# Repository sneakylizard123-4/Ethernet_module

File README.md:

# W5500 Ethernet Module

A small SPI Ethernet breakout for the W5500.

## Features

- SPI interface
- 10/100 Ethernet
- 4-layer board with ground and 3.3V planes
- Split analog/digital supply with ferrite bead
- On-board and jack LEDs
- 25 MHz crystal

## PCB

50.0 x 21.4 mm, 4-layer, 1.6 mm FR-4.

## Schematic

## Pinout

| Pin | Name | Notes |
|---|---|---|
| 1 | GND | Ground |
| 2 | 3.3V | Power in |
| 3 | SCS | Chip select (active low) |
| 4 | SCLK | SPI clock |
| 5 | MISO | SPI MISO |
| 6 | MOSI | SPI MOSI |
| 7 | INT | Interrupt (active low) |
| 8 | RST | Reset (active low) |

## BOM

| Ref | Value | MPN | Manufacturer | Qty | Unit $ | Ext $ | Supplier Link |
|-----|-------|-----|--------------|-----|--------|-------|---------------|
| C1,C4,C6,C8,C10,C11,C13 | 0.1uF 50V X7R 0603 | CL10B104KB8NNNC | Samsung Electro-Mechanics | 7 | 0.0088 | 0.0616 | [LCSC](https://www.lcsc.com/product-detail/Samsung-Electro-Mechanics-CL10B104KB8NNNC_C1591.html) |
| C9,C12 | 18pF 50V C0G 0603 | 0603N180J500CT | Union Semiconductor | 2 | 0.0069 | 0.0138 | [LCSC](https://www.lcsc.com/product-detail/Union-Semiconductor-0603N180J500CT_C123538.html) |
| C5,C14 | 10nF 50V X7R 0603 | CL10B103KB8NNNC | Samsung Electro-Mechanics | 2 | 0.0103 | 0.0206 | [LCSC](https://www.lcsc.com/product-detail/Samsung-Electro-Mechanics-CL10B103KB8NNNC_C1589.html) |
| C15,C17 | 6.8nF 50V X7R 0603 | CL10B682JB8NNNC | Samsung Electro-Mechanics | 2 | 0.0075 | 0.0150 | [LCSC](https://www.lcsc.com/product-detail/Samsung-Electro-Mechanics-CL10B682JB8NNNC_C307492.html) |
| C16 | 22nF 50V X7R 0603 | CC0603KRX7R9BB223 | Yageo | 1 | 0.0063 | 0.0063 | [LCSC](https://www.lcsc.com/product-detail/YAGEO-CC0603KRX7R9BB223_C106222.html) |
| C2,C3 | 10uF 10V X5R 0603 | CL10A106KP8NNNC | Samsung Electro-Mechanics | 2 | 0.0322 | 0.0644 | [LCSC](https://www.lcsc.com/product-detail/Samsung-Electro-Mechanics-CL10A106KP8NNNC_C19702.html) |
| C7 | 4.7uF 10V X5R 0603 | CL10A475KP8NNNC | Samsung Electro-Mechanics | 1 | 0.0164 | 0.0164 | [LCSC](https://www.lcsc.com/product-detail/Samsung-Electro-Mechanics-CL10A475KP8NNNC_C1705.html) |
| D1,D2 | LED red high-efficiency 0603 | KT-0603R | Keystone Electronics | 2 | 0.0076 | 0.0152 | [LCSC](https://www.lcsc.com/product-detail/Keystone-Electronics-KT-0603R_C2286.html) |
| FB1 | Ferrite bead 120R 0603 | CBW160808U121T | Sunlord | 1 | 0.0086 | 0.0086 | [LCSC](https://www.lcsc.com/product-detail/Sunlord-CBW160808U121T_C139175.html) |
| J1 | RJ45 magjack HFJ11-2450E-L11RL | HFJ11-2450E-L11RL | Halo Electronics | 1 | 5.2300 | 5.2300 | [DigiKey](https://www.digikey.com/en/products/detail/halo-electronics-inc/HFJ11-2450E-L11RL/25658121) |
| J2 | Header 1x08 2.54mm | 2.54-1*8 | CONNFLY Elec | 1 | 0.0442 | 0.0442 | [LCSC](https://www.lcsc.com/product-detail/CONNFLY-Elec-2-54-1-8_C5156616.html) |
| R1 | 12.4k 1% 0603 | 0603WAF1242T5E | UniRoyal Elec | 1 | 0.0015 | 0.0015 | [LCSC](https://www.lcsc.com/product-detail/UNI-ROYAL-Uniroyal-Elec-0603WAF1242T5E_C22865.html) |
| R2,R3 | 1k 1% 0603 | 0603WAF1001T5E | UniRoyal Elec | 2 | 0.0026 | 0.0052 | [LCSC](https://www.lcsc.com/product-detail/UNI-ROYAL-Uniroyal-Elec-0603WAF1001T5E_C21190.html) |
| R4,R5,R6,R7 | 49.9R 1% 0603 | RC0603FR-0749R9L | Yageo | 4 | 0.0062 | 0.0248 | [LCSC](https://www.lcsc.com/product-detail/YAGEO-RC0603FR-0749R9L_C114625.html) |
| R8 | 10R 1% 0603 | 0603WAF100JT5E | UniRoyal Elec | 1 | 0.0032 | 0.0032 | [LCSC](https://www.lcsc.com/product-detail/UNI-ROYAL-Uniroyal-Elec-0603WAF100JT5E_C22859.html) |
| R9,R10 | 330R 1% 0603 | 0603WAF3300T5E | UniRoyal Elec | 2 | 0.0026 | 0.0052 | [LCSC](https://www.lcsc.com/product-detail/UNI-ROYAL-Uniroyal-Elec-0603WAF3300T5E_C23138.html) |
| RN1 | 0R array 0603x4 | 4D03WGJ0000T5E | UniRoyal Elec | 1 | 0.0090 | 0.0090 | [LCSC](https://www.lcsc.com/product-detail/UNI-ROYAL-Uniroyal-Elec-4D03WGJ0000T5E_C1952.html) |
| U1 | W5500 LQFP-48 | W5500 | WIZnet | 1 | 2.8503 | 2.8503 | [LCSC](https://www.lcsc.com/product-detail/WIZnet-W5500_C32843.html) |
| X1 | 25MHz 3225 | TXC-7A-25.000MBB-T | TXC Corporation | 1 | 0.0954 | 0.0954 | [LCSC](https://www.lcsc.com/product-detail/TXC-Corp-TXC-7A-25-000MBB-T_C9006.html) |
| PCB | 50.0x21.4mm 4-layer FR-4 (5 pcs, est.) | - | JLCPCB | 5 | 2.0000 | 10.0000 | [JLCPCB](https://jlcpcb.com/) |
| **Total (parts per 1 board)** | | | | | | **8.49** | |
| **Grand total (5 boards: parts + PCBs)** | | | | | | **52.45** | |

Full BOM: [BOM.csv](BOM.csv)

## Production

Gerbers, drill files, STEP, IPC netlists, and placement files are in `kicad/production/`.

## Known issues

- The RJ45 mating face is ~6.1 mm closer to the board center than Halo recommends. Check case clearances.
- No mounting holes.

## License

Hardware: CERN-OHL-S-2.0. This covers the board design and the reconstructed 3D model for the magjack.

Based on WIZnet's W5500 reference design.

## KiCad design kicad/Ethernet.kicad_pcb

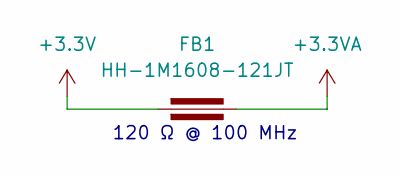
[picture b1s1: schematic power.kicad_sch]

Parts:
FB1: HH-1M1608-121JT; Fuse_0603_1608Metric

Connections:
+3.3V: FB1.1; also elsewhere on the board
+3.3VA: FB1.2; also elsewhere on the board

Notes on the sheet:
120 Ω @ 100 MHz

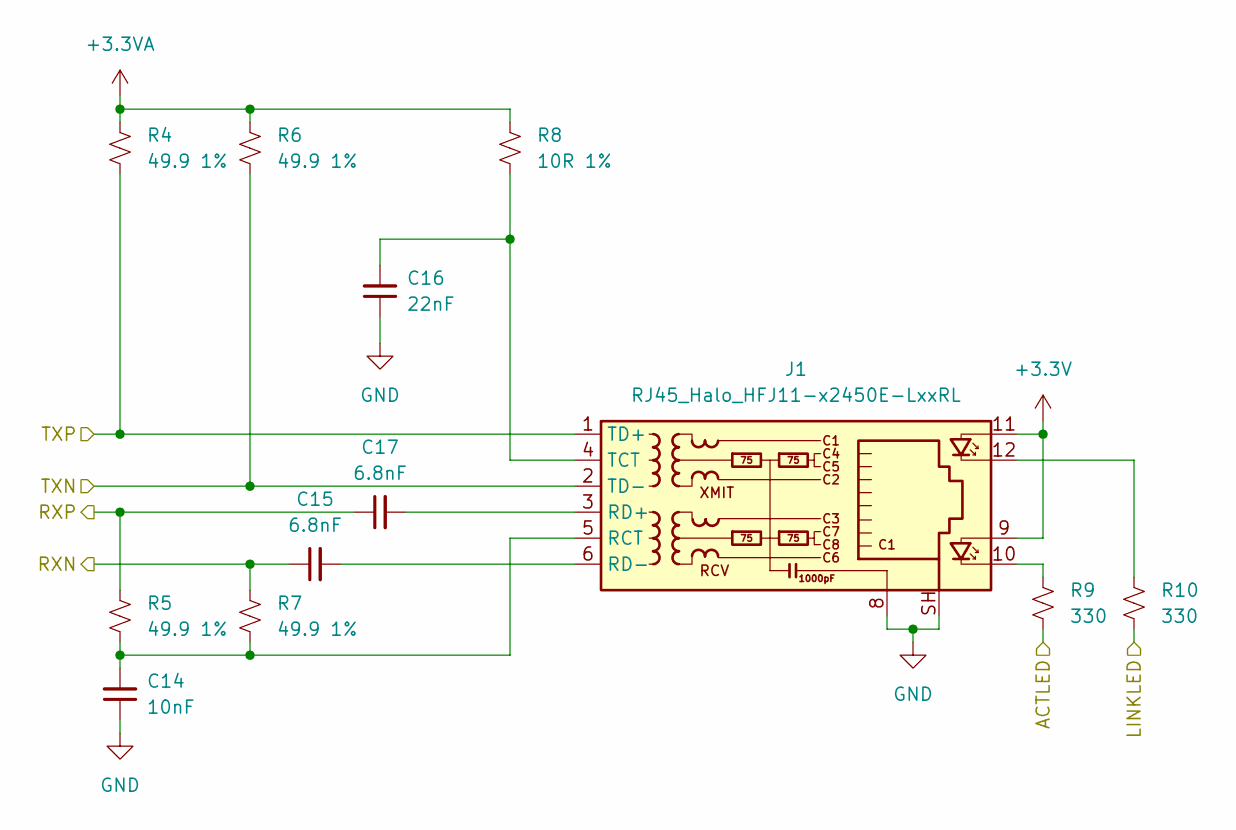
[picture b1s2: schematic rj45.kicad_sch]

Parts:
C14: 10nF; C_0603_1608Metric
C15, C17: 6.8nF; C_0603_1608Metric
C16: 22nF; C_0603_1608Metric
J1: RJ45_Halo_HFJ11-x2450E-LxxRL; RJ45_HALO_HFJ11-x2450E-LxxRL_Horizontal
R4, R5, R6, R7: 49.9 1%; R_0603_1608Metric
R8: 10R 1%; R_0603_1608Metric
R9, R10: 330; R_0603_1608Metric

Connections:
+3.3V: J1.9, J1.11; also elsewhere on the board
+3.3VA: R4.1, R6.1, R8.1; also elsewhere on the board
/RJ45/ACTLED: R9.1; also elsewhere on the board
/RJ45/LINKLED: R10.1; also elsewhere on the board
/RJ45/RXN: C15.1, R7.1; also elsewhere on the board
/RJ45/RXP: C17.1, R5.1; also elsewhere on the board
/RJ45/TXN: J1.2 (TD-), R6.2; also elsewhere on the board
/RJ45/TXP: J1.1 (TD+), R4.2; also elsewhere on the board
GND: C14.1, C16.1, J1.8, J1.SH; also elsewhere on the board
unnamed: J1.10, R9.2
unnamed: J1.12, R10.2
unnamed: C14.2, J1.5 (RCT), R5.2, R7.2
unnamed: C17.2, J1.3 (RD+)
unnamed: C15.2, J1.6 (RD-)
unnamed: C16.2, J1.4 (TCT), R8.2

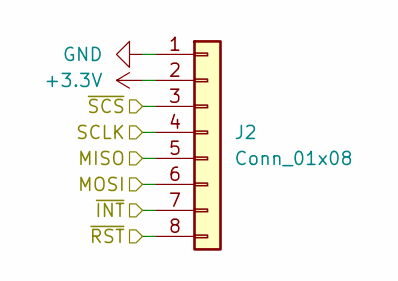
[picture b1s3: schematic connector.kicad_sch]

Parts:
J2: Conn_01x08; PinHeader_1x08_P2.54mm_Vertical

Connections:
+3.3V: J2.2; also elsewhere on the board
/Connector/MISO: J2.5; also elsewhere on the board
/Connector/MOSI: J2.6; also elsewhere on the board
/Connector/SCLK: J2.4; also elsewhere on the board
/Connector/~INT: J2.7; also elsewhere on the board
/Connector/~RST: J2.8; also elsewhere on the board
/Connector/~SCS: J2.3; also elsewhere on the board
GND: J2.1; also elsewhere on the board

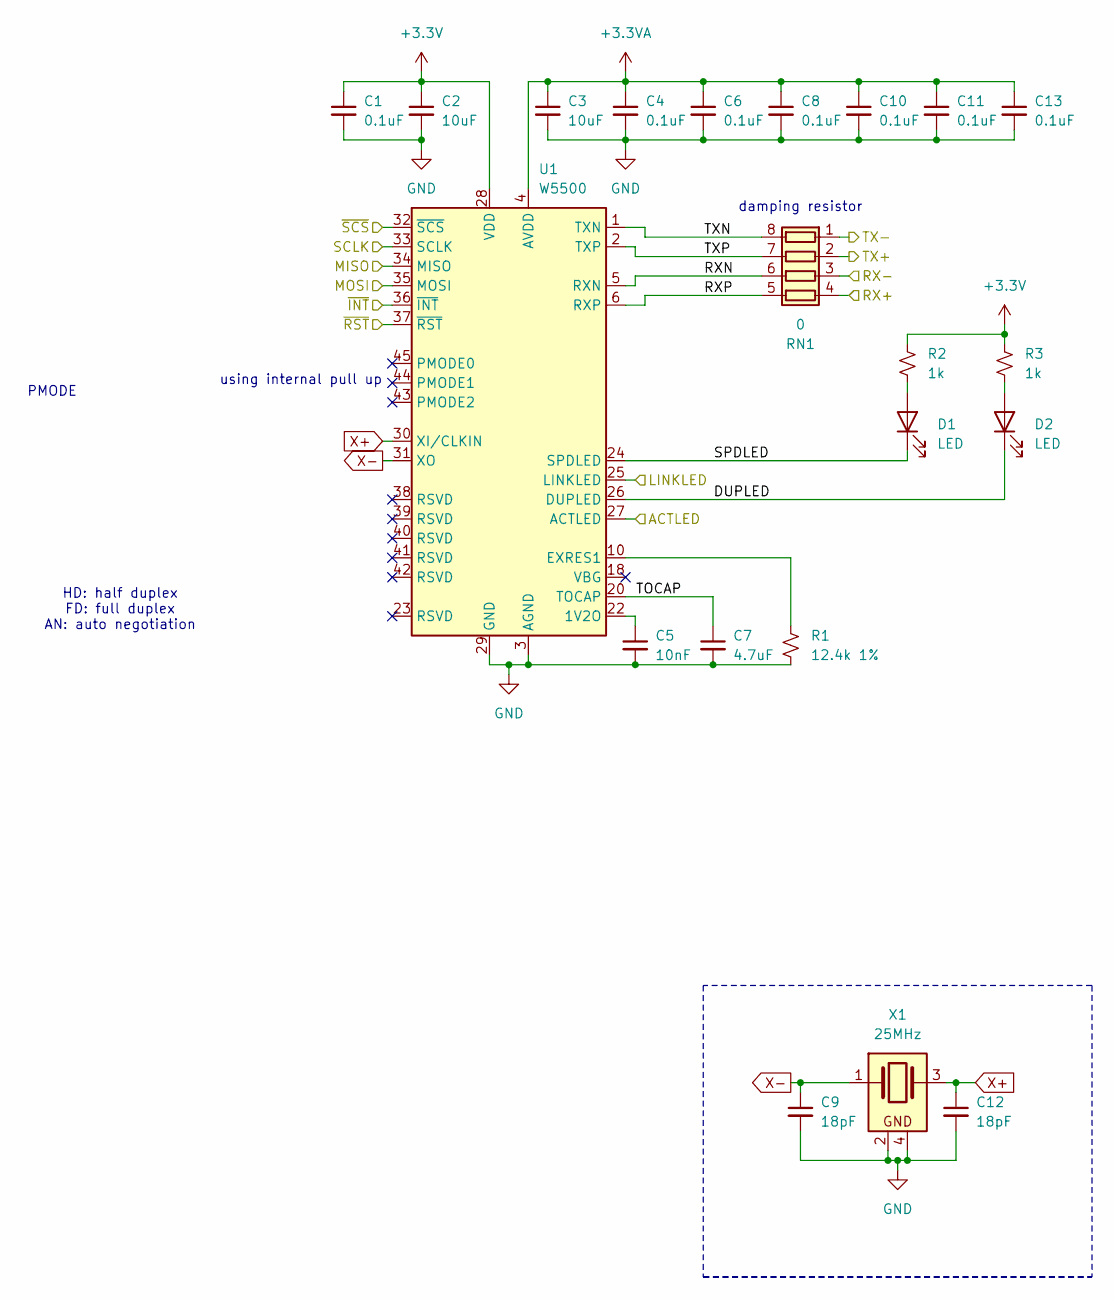
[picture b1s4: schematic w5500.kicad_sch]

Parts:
C1, C4, C6, C8, C10, C11, C13: 0.1uF; C_0603_1608Metric
C2, C3: 10uF; C_0603_1608Metric
C5: 10nF; C_0603_1608Metric
C7: 4.7uF; C_0603_1608Metric
C9, C12: 18pF; C_0603_1608Metric
D1, D2: LED; LED_0603_1608Metric
R1: 12.4k 1%; R_0603_1608Metric
R2, R3: 1k; R_0603_1608Metric
RN1: 0; R_Array_Convex_4x0603
U1: W5500; LQFP-48_7x7mm_P0.5mm
X1: 25MHz; Crystal_SMD_3225-4Pin_3.2x2.5mm

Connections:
+3.3V: C1.1, C2.1, R2.1, R3.1, U1.28 (VDD); also elsewhere on the board
+3.3VA: C3.1, C4.1, C6.1, C8.1, C10.1, C11.1, C13.1, U1.4 (AVDD), U1.8 (AVDD), U1.11 (AVDD), U1.15 (AVDD), U1.17 (AVDD), U1.21 (AVDD); also elsewhere on the board
/Connector/MISO: U1.34 (MISO); also elsewhere on the board
/Connector/MOSI: U1.35 (MOSI); also elsewhere on the board
/Connector/SCLK: U1.33 (SCLK); also elsewhere on the board
/Connector/~INT: U1.36 (~INT); also elsewhere on the board
/Connector/~RST: U1.37 (~RST); also elsewhere on the board
/Connector/~SCS: U1.32 (~SCS); also elsewhere on the board
/RJ45/ACTLED: U1.27 (ACTLED); also elsewhere on the board
/RJ45/LINKLED: U1.25 (LINKLED); also elsewhere on the board
/RJ45/RXN: RN1.3 (R3.1); also elsewhere on the board
/RJ45/RXP: RN1.4 (R4.1); also elsewhere on the board
/RJ45/TXN: RN1.1 (R1.1); also elsewhere on the board
/RJ45/TXP: RN1.2 (R2.1); also elsewhere on the board
/W5500/DUPLED: D2.1 (K), U1.26 (DUPLED)
/W5500/RXN: RN1.6 (R3.2), U1.5 (RXN)
/W5500/RXP: RN1.5 (R4.2), U1.6 (RXP)
/W5500/SPDLED: D1.1 (K), U1.24 (SPDLED)
/W5500/TOCAP: C7.1, U1.20 (TOCAP)
/W5500/TXN: RN1.8 (R1.2), U1.1 (TXN)
/W5500/TXP: RN1.7 (R2.2), U1.2 (TXP)
GND: C1.2, C2.2, C3.2, C4.2, C5.2, C6.2, C7.2, C8.2, C9.2, C10.2, C11.2, C12.2, C13.2, R1.2, U1.3 (AGND), U1.9 (AGND), U1.14 (AGND), U1.16 (AGND), U1.19 (AGND), U1.29 (GND), U1.48 (AGND), X1.2, X1.4; also elsewhere on the board
unnamed: D1.2 (A), R2.2
unnamed: D2.2 (A), R3.2
unnamed: C5.1, U1.22 (1V2O)
unnamed: R1.1, U1.10 (EXRES1)
X+: C12.1, U1.30 (XI/CLKIN), X1.3
X-: C9.1, U1.31 (XO), X1.1

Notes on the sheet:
PMODE
using internal pull up
damping resistor
HD: half duplex FD: full duplex AN: auto negotiation

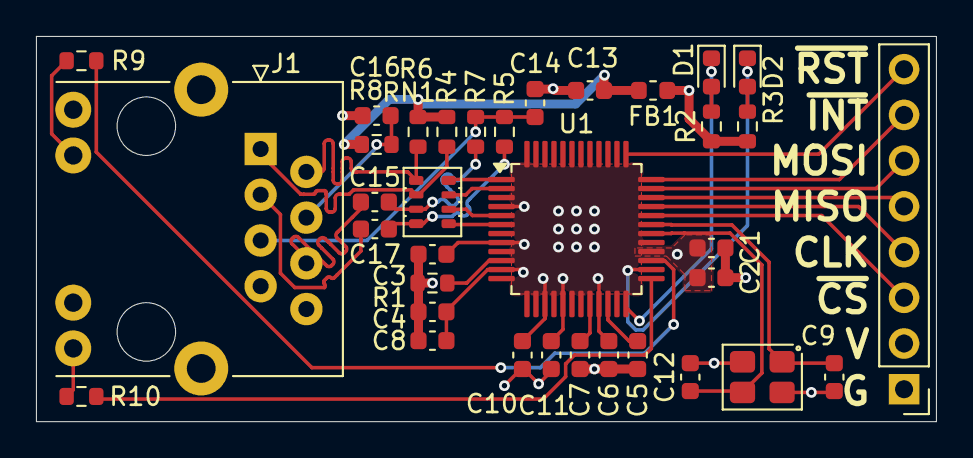
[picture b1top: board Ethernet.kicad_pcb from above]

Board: 4 copper layers, 50.0 x 21.4 mm, 35 parts (0 on the bottom side), 34 nets.

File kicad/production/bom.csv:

Designator,Footprint,Quantity,Value,LCSC Part #
"C1, C10, C11, C13, C4, C6, C8",0603,7,0.1uF,
"C12, C9",0603,2,18pF,
"C14, C5",0603,2,10nF,
"C15, C17",0603,2,6.8nF,
C16,0603,1,22nF,
"C2, C3",0603,2,10uF,
C7,0603,1,4.7uF,
"D1, D2",0603,2,LED,
FB1,0603,1,HH-1M1608-121JT,
J1,RJ45_HALO_HFJ11-x2450E-LxxRL_Horizontal,1,RJ45_Halo_HFJ11-x2450E-LxxRL,
J2,PinHeader_1x08_P2.54mm_Vertical,1,Conn_01x08,
R1,0603,1,12.4k 1%,
"R10, R9",0603,2,330,
"R2, R3",0603,2,1k,
"R4, R5, R6, R7",0603,4,49.9 1%,
R8,0603,1,10R 1%,
RN1,R_Array_Convex_4x0603,1,0,
U1,LQFP-48_7x7mm_P0.5mm,1,W5500,
X1,Crystal_SMD_3225-4Pin_3.2x2.5mm,1,25MHz,
